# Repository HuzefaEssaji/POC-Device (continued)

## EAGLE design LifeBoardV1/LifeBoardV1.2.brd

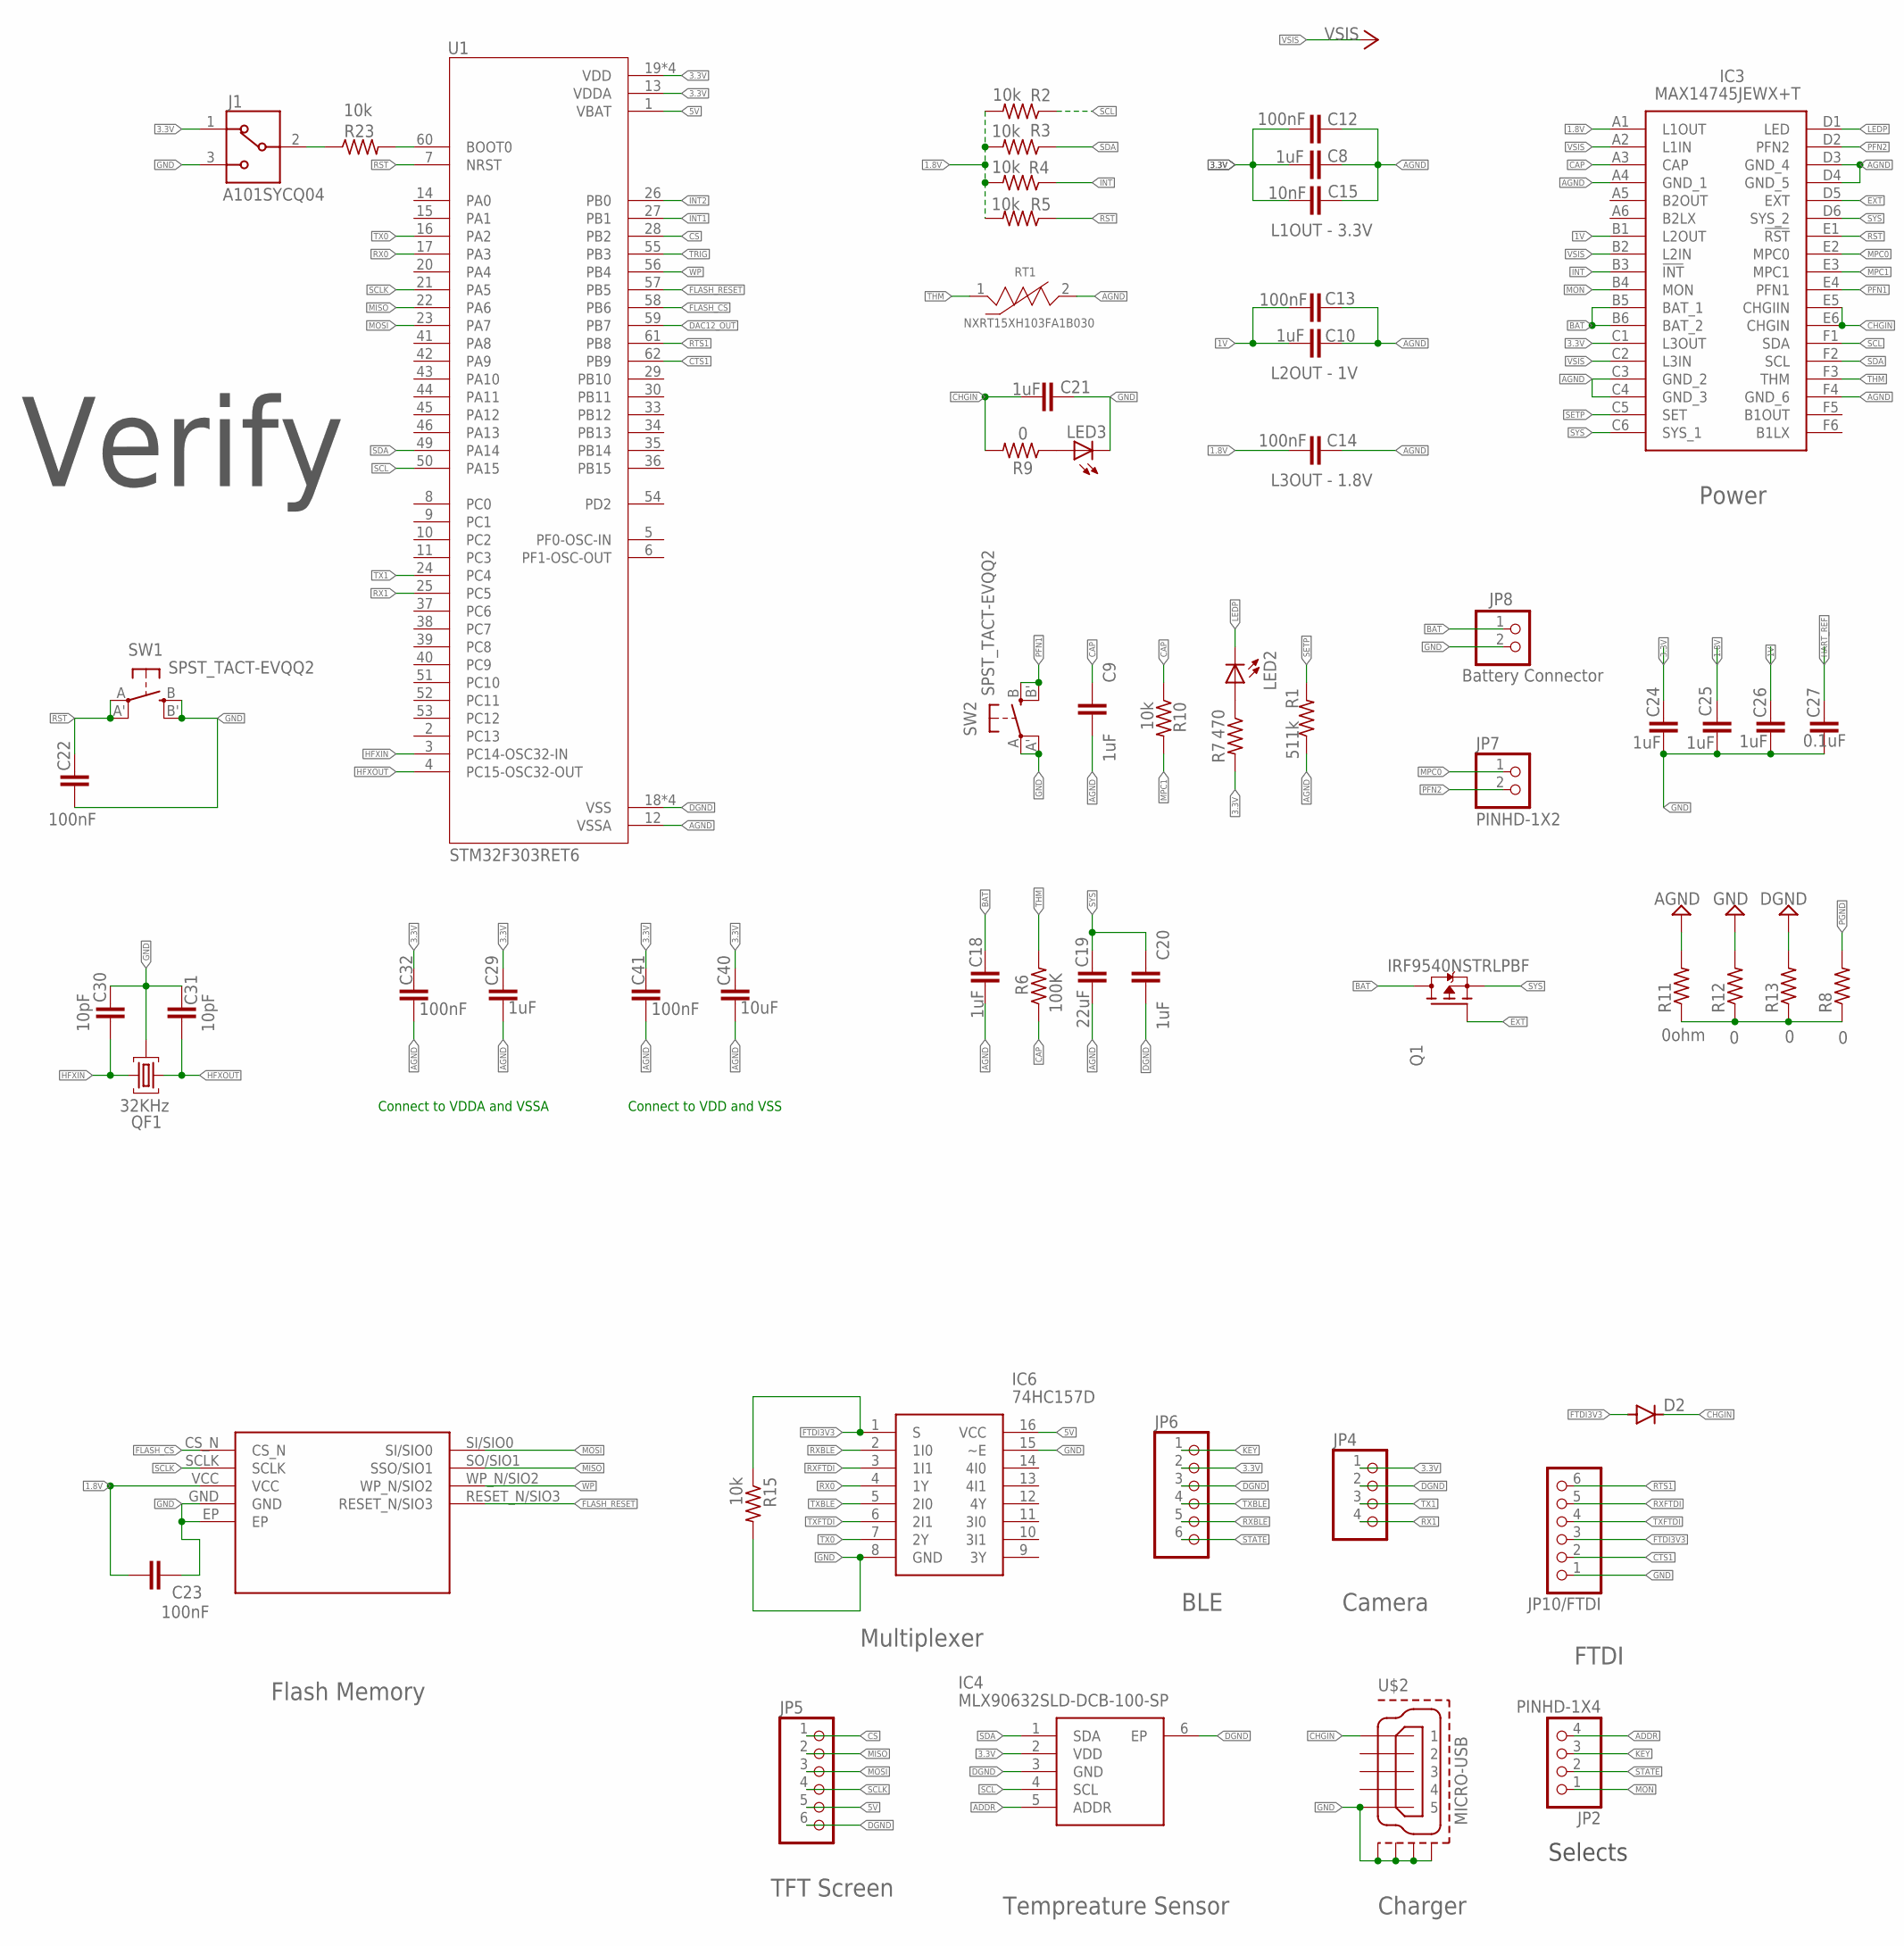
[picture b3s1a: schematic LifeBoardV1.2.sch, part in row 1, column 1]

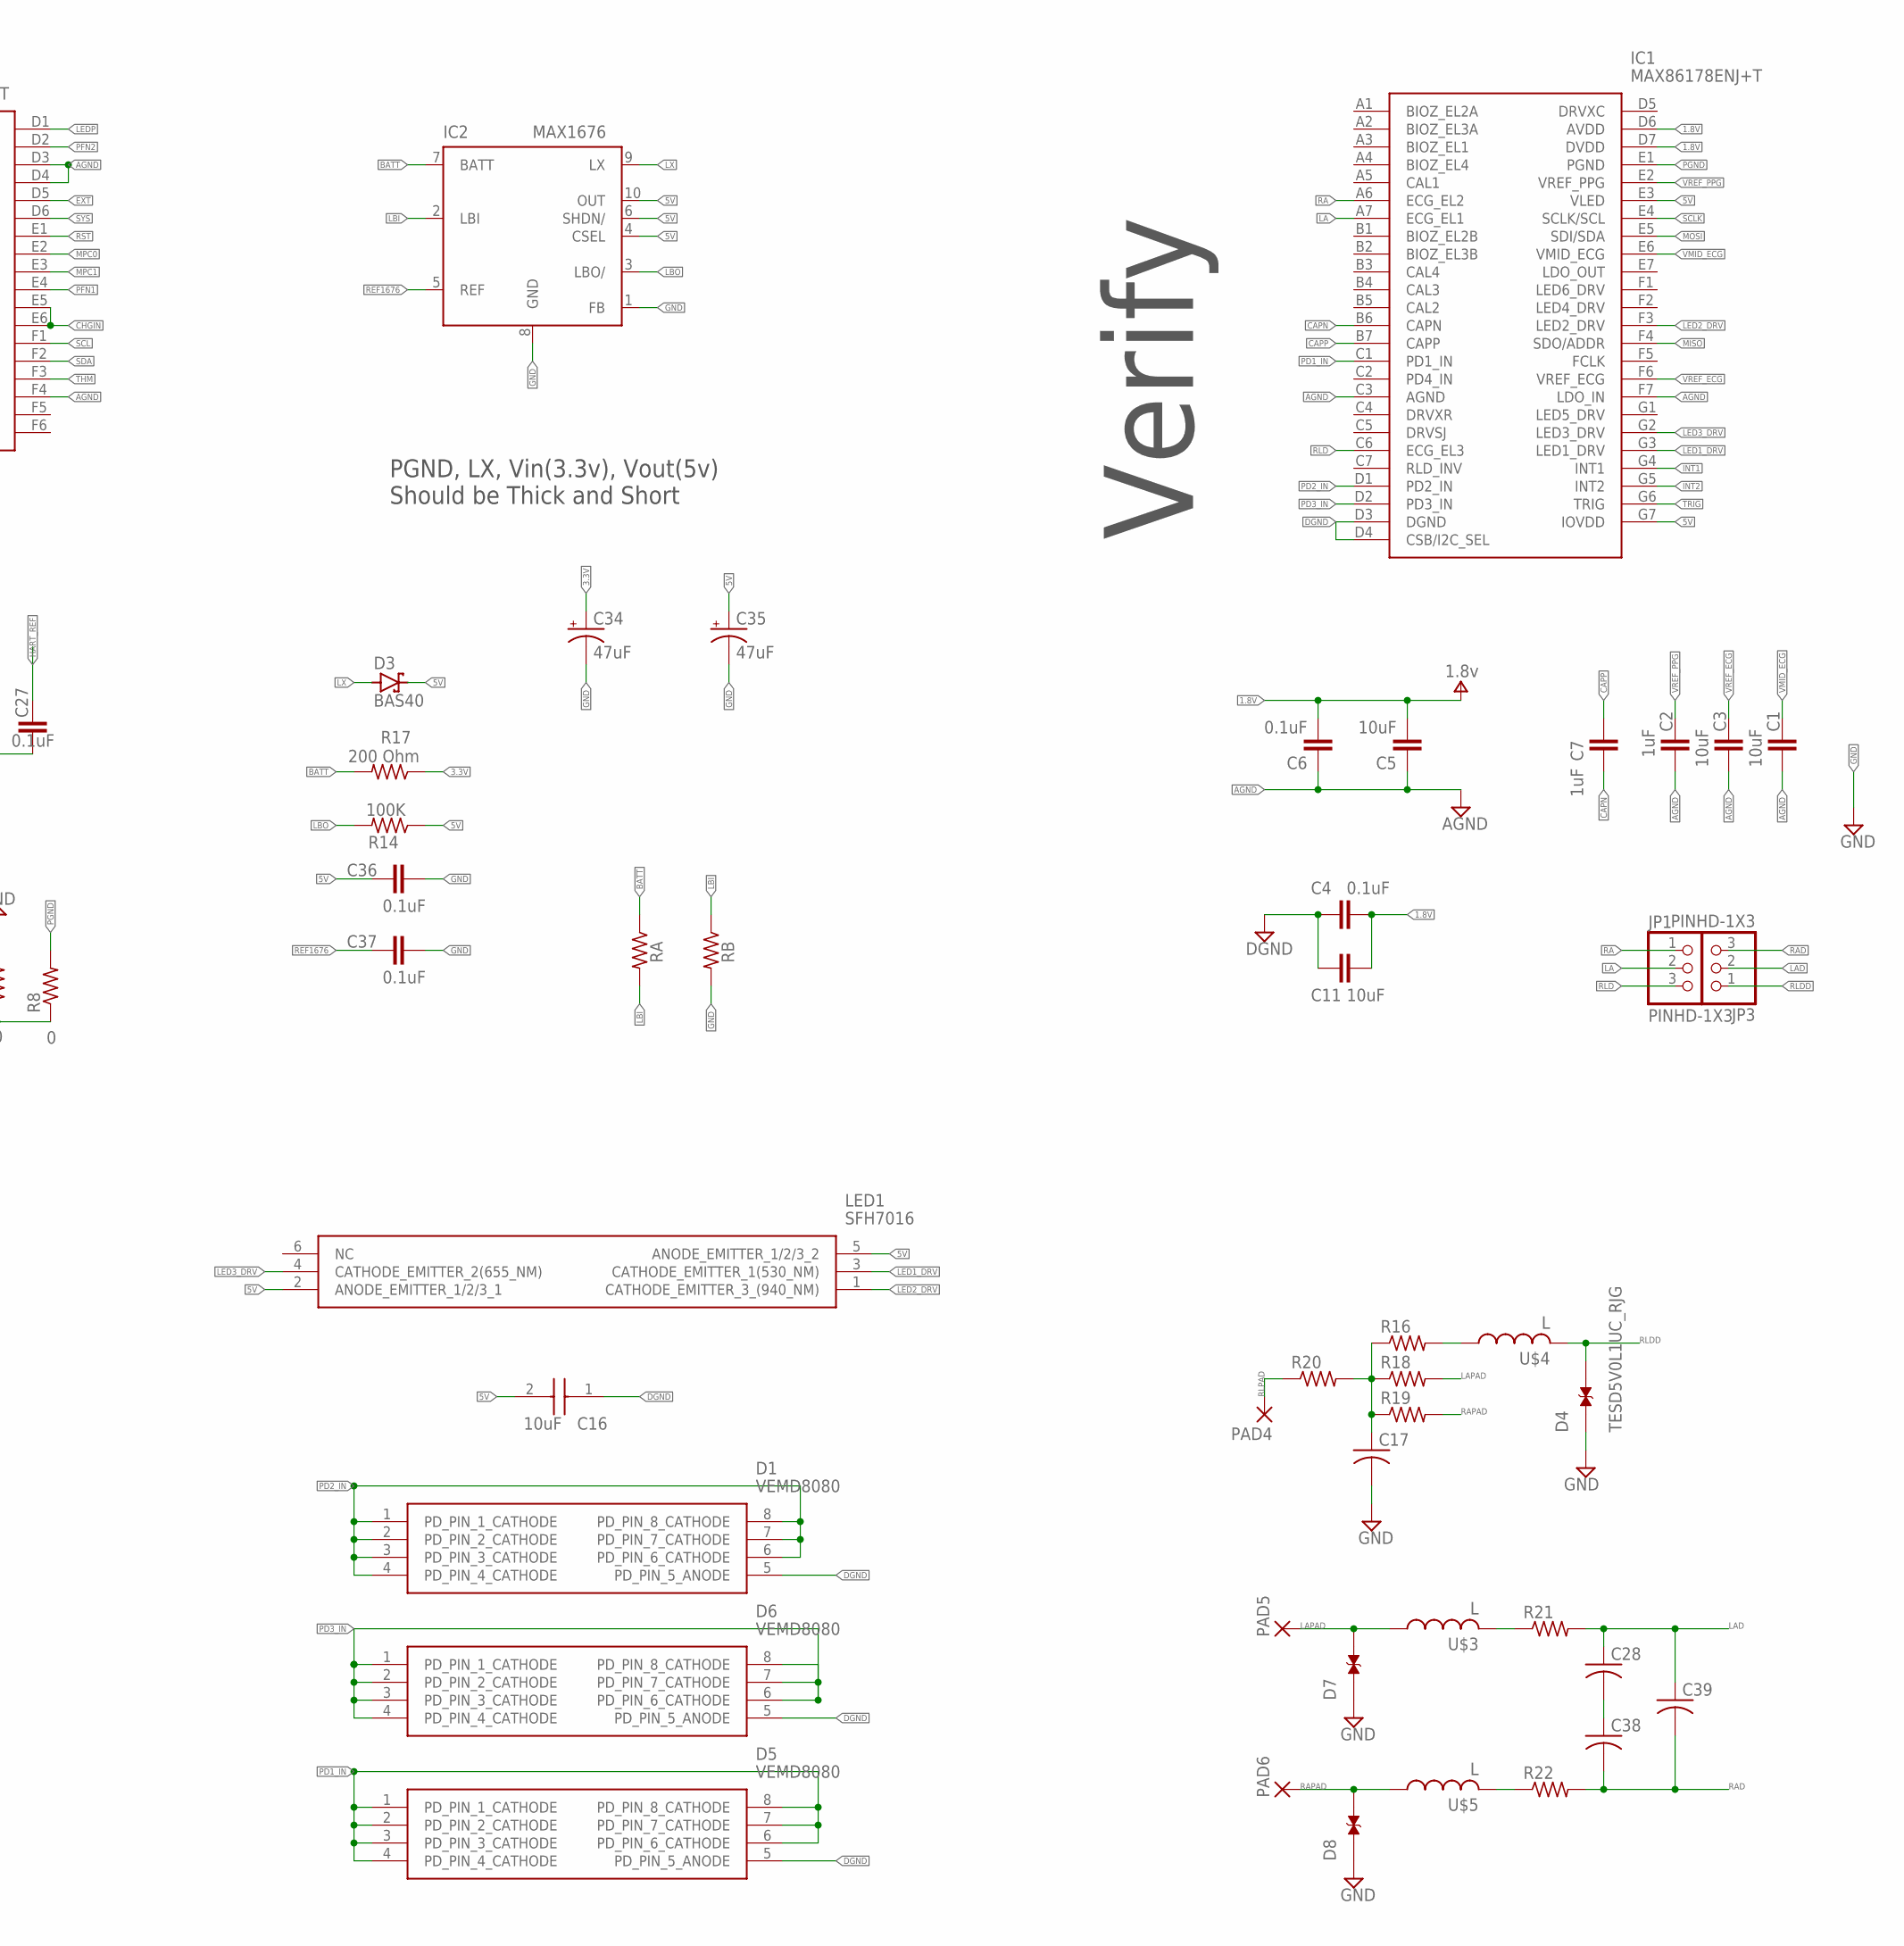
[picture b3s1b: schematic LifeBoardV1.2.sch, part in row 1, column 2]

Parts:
C1, C3, C5, C11, C40: 10uF; C0805
C2, C7, C8, C9, C10, C18, C20, C21, C24, C25, C26, C29: 1uF; C0805
C4, C6, C27, C36, C37: 0.1uF; C0805
C12, C13, C14, C22, C23, C32, C41: 100nF; C0805
C15: 10nF; C0805
C16: 10uF; CAPC1608X90N
C17, C28, C38, C39: C-US025-024X044; C025-024X044
C19: 22uF; C0805
C30, C31: 10pF; C0805
C34, C35: 47uF; 153CLV-0405
D1, D5, D6: VEMD8080
D2: CGRM4001-G; SOD-123_MINI-SMA
D3: BAS40; SOT23
D4, D7, D8: TESD5V0L1UC_RJG; DIO_TESD5V0L1UC_RJG
IC1: MAX86178ENJ+T; BGA49C35P7X7_277X257X50
IC2: MAX1676; UMAX10
IC3: MAX14745JEWX+T; BGA36C40P6X6_269X244X69
IC4: MLX90632SLD-DCB-100-SP; MLX90632SLDDCB100SP
IC6: 74HC157D; SOIC127P600X175-16N
J1: A101SYCQ04; TE_A101SYCQ04
JP1, JP3: PINHD-1X3; 1X03
JP2, JP4: PINHD-1X4; 1X04
JP5, JP6, JP10/FTDI: PINHD-1X6; 1X06
JP7: PINHD-1X2; 1X02
JP8: Battery Connector; 1X02
LED1: SFH7016
LED2, LED3: LEDCHIPLED_1206; CHIPLED_1206
PAD4, PAD5, PAD6: SMD5; SMD2,54-5,08
Q1: IRF9540NSTRLPBF; DPAK254P1524X483-4_3N
QF1: 32KHz; HC49U
R1: 511k; M1206
R2, R3, R4, R5, R10, R15, R23: 10k; M1206
R6: 100K; M1206
R7: 470; M1206
R8, R9, R12, R13: 0; R1206
R11: 0ohm; R1206
R14: 100K; R1206
R16, R18, R19, R20, R21, R22: R-US_0207/10; 0207/10
R17: 200 Ohm; R1206
RA: R-US_R1206; R1206
RB: R-US_R1206; R1206
RT1: NXRT15XH103FA1B030; THERM_NXRT15XH103FA1B030
SW1, SW2: SPST_TACT-EVQQ2; EVQ-Q2
U1: STM32F303RET6; QFP50P1200X1200X160-64N
U$1: FLASH; SON127P600X800X80-9N
U$2: MICRO-USB; 47589-0001
U$3, U$4, U$5: L; 6000

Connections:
1.8V: C4.2, C5.2, C6.2, C11.2, C14.2, C23.1, C25.1, IC1.D6 (AVDD), IC1.D7 (DVDD), IC3.A1 (L1OUT), R2.2, R3.2, R4.2, R5.2, U$1.VCC
1V: C10.2, C13.2, C26.1, IC3.B1 (L2OUT)
3.3V: C8.2, C12.2, C15.2, C24.1, C29.1, C32.1, C34.+, C40.1, C41.1, IC3.C1 (L3OUT), IC4.2 (VDD), J1.1, JP4.1, JP6.2, R7.2, R17.1, U1.13 (VDDA), U1.19 (VDD), U1.32 (VDD), U1.48 (VDD), U1.64 (VDD)
5V: C16.2, C35.+, C36.1, D3.3 (C), IC1.E3 (VLED), IC1.G7 (IOVDD), IC2.4 (CSEL), IC2.6 (SHDN/), IC2.10 (OUT), IC6.16 (VCC), JP5.5, LED1.2 (ANODE_EMITTER_1/2/3_1), LED1.5 (ANODE_EMITTER_1/2/3_2), R14.1, U1.1 (VBAT)
ADDR: IC4.5 (ADDR), JP2.4
AGND: C1.1, C2.1, C3.1, C5.1, C6.1, C8.1, C9.2, C10.1, C12.1, C13.1, C14.1, C15.1, C18.2, C19.2, C29.2, C32.2, C40.2, C41.2, IC1.C3 (AGND), IC1.F7 (LDO_IN), IC3.A4 (GND_1), IC3.C3 (GND_2), IC3.C4 (GND_3), IC3.D3 (GND_4), IC3.D4 (GND_5), IC3.F4 (GND_6), R1.1, R11.2, RT1.2, U1.12 (VSSA)
BAT: C18.1, IC3.B5 (BAT_1), IC3.B6 (BAT_2), JP8.1, Q1.4 (D)
BATT: IC2.7 (BATT), R17.2, RA.1
CAP: C9.1, IC3.A3 (CAP), R6.1, R10.1
CAPN: C7.2, IC1.B6 (CAPN)
CAPP: C7.1, IC1.B7 (CAPP)
CHGIN: C21.2, D2.C, IC3.E5 (CHGIIN), IC3.E6 (CHGIN), R9.2, U$2.1
CS: JP5.1, U1.28 (PB2)
CTS1: JP10/FTDI.2, U1.62 (PB9)
DAC12_OUT: U1.59 (PB7)
DGND: C4.1, C11.1, C16.1, C20.2, D1.5 (PD_PIN_5_ANODE), D5.5 (PD_PIN_5_ANODE), D6.5 (PD_PIN_5_ANODE), IC1.D3 (DGND), IC1.D4 (CSB/I2C_SEL), IC4.3 (GND), IC4.6 (EP), JP4.2, JP5.6, JP6.3, R13.2, U1.18 (VSS), U1.31 (VSS), U1.47 (VSS), U1.63 (VSS)
EXT: IC3.D5 (EXT), Q1.1 (G)
FLASH_CS: U1.58 (PB6), U$1.CS_N
FLASH_RESET: U1.57 (PB5), U$1.RESET_N/SIO3
FTDI3V3: D2.A, IC6.1 (S), JP10/FTDI.3, R15.1
GND: C17.2, C21.1, C22.2, C23.2, C24.2, C25.2, C26.2, C27.2, C30.1, C31.1, C34.-, C35.-, C36.2, C37.2, D4.1, D7.1, D8.1, IC2.1 (FB), IC2.8 (GND), IC6.8 (GND), IC6.15 (~E), J1.3, JP8.2, JP10/FTDI.1, LED3.C, QF1.2, R12.2, R15.2, RB.2, SW1.B (S), SW1.B' (S1), SW2.A, SW2.A' (P1), U$1.EP, U$1.GND, U$2.5, U$2.CASING1 (GND1), U$2.CASING2 (GND2), U$2.CASING3 (GND3), U$2.CASING4 (GND4)
HART_REF: C27.1
HFXIN: C30.2, QF1.3, U1.3 (PC14-OSC32-IN)
HFXOUT: C31.2, QF1.1, U1.4 (PC15-OSC32-OUT)
INT: IC3.B3 (!INT), R4.1
INT1: IC1.G4 (INT1), U1.27 (PB1)
INT2: IC1.G5 (INT2), U1.26 (PB0)
KEY: JP2.3, JP6.1
LA: IC1.A7 (ECG_EL1), JP1.2
LAD: C28.1, C39.1, JP3.2, R21.2
LAPAD: D7.2, PAD5.1, R18.2, U$3.1
LBI: IC2.2 (LBI), RA.2, RB.1
LBO: IC2.3 (LBO/), R14.2
LED1_DRV: IC1.G3 (LED1_DRV), LED1.3 (CATHODE_EMITTER_1(530_NM))
LED2_DRV: IC1.F3 (LED2_DRV), LED1.1 (CATHODE_EMITTER_3_(940_NM))
LED3_DRV: IC1.G2 (LED3_DRV), LED1.4 (CATHODE_EMITTER_2(655_NM))
LEDP: IC3.D1 (LED), LED2.C
LX: D3.1 (A), IC2.9 (LX)
MISO: IC1.F4 (SDO/ADDR), JP5.2, U1.22 (PA6), U$1.SO/SIO1 (SSO/SIO1)
MON: IC3.B4 (MON), JP2.1
MOSI: IC1.E5 (SDI/SDA), JP5.3, U1.23 (PA7), U$1.SI/SIO0
MPC0: IC3.E2 (MPC0), JP7.1
MPC1: IC3.E3 (MPC1), R10.2
unnamed: LED2.A, R7.1
unnamed: C17.1, R16.1, R18.1, R19.1, R20.2
unnamed: R16.2, U$4.1
unnamed: R23.2, U1.60 (BOOT0)
unnamed: J1.2, R23.1
unnamed: R21.1, U$3.2
unnamed: C28.2, C38.1
unnamed: R22.1, U$5.2
unnamed: R8.1, R11.1, R12.1, R13.1
unnamed: LED3.A, R9.1
PD1_IN: D5.1 (PD_PIN_1_CATHODE), D5.2 (PD_PIN_2_CATHODE), D5.3 (PD_PIN_3_CATHODE), D5.4 (PD_PIN_4_CATHODE), D5.6 (PD_PIN_6_CATHODE), D5.7 (PD_PIN_7_CATHODE), D5.8 (PD_PIN_8_CATHODE), IC1.C1 (PD1_IN)
PD2_IN: D1.1 (PD_PIN_1_CATHODE), D1.2 (PD_PIN_2_CATHODE), D1.3 (PD_PIN_3_CATHODE), D1.4 (PD_PIN_4_CATHODE), D1.6 (PD_PIN_6_CATHODE), D1.7 (PD_PIN_7_CATHODE), D1.8 (PD_PIN_8_CATHODE), IC1.D1 (PD2_IN)
PD3_IN: D6.1 (PD_PIN_1_CATHODE), D6.2 (PD_PIN_2_CATHODE), D6.3 (PD_PIN_3_CATHODE), D6.4 (PD_PIN_4_CATHODE), D6.6 (PD_PIN_6_CATHODE), D6.7 (PD_PIN_7_CATHODE), D6.8 (PD_PIN_8_CATHODE), IC1.D2 (PD3_IN)
PFN1: IC3.E4 (PFN1), SW2.B (S), SW2.B' (S1)
PFN2: IC3.D2 (PFN2), JP7.2
PGND: IC1.E1 (PGND), R8.2
RA: IC1.A6 (ECG_EL2), JP1.1
RAD: C38.2, C39.2, JP3.3, R22.2
RAPAD: D8.2, PAD6.1, R19.2, U$5.1
REF1676: C37.1, IC2.5 (REF)
RLD: IC1.C6 (ECG_EL3), JP1.3
RLDD: D4.2, JP3.1, U$4.2
RLPAD: PAD4.1, R20.1
RST: C22.1, IC3.E1 (!RST), R5.1, SW1.A, SW1.A' (P1), U1.7 (NRST)
RTS1: JP10/FTDI.6, U1.61 (PB8)
RX0: IC6.4 (1Y), U1.17 (PA3)
RX1: JP4.4, U1.25 (PC5)
RXBLE: IC6.2 (1I0), JP6.5
RXFTDI: IC6.3 (1I1), JP10/FTDI.5
SCL: IC3.F1 (SDA), IC4.4 (SCL), R2.1, U1.50 (PA15)
SCLK: IC1.E4 (SCLK/SCL), JP5.4, U1.21 (PA5), U$1.SCLK
SDA: IC3.F2 (SCL), IC4.1 (SDA), R3.1, U1.49 (PA14)
SETP: IC3.C5 (SET), R1.2
STATE: JP2.2, JP6.6
SYS: C19.1, C20.1, IC3.C6 (SYS_1), IC3.D6 (SYS_2), Q1.3 (S)
THM: IC3.F3 (THM), R6.2, RT1.1
TRIG: IC1.G6 (TRIG), U1.55 (PB3)
TX0: IC6.7 (2Y), U1.16 (PA2)
TX1: JP4.3, U1.24 (PC4)
TXBLE: IC6.5 (2I0), JP6.4
TXFTDI: IC6.6 (2I1), JP10/FTDI.4
VMID_ECG: C1.2, IC1.E6 (VMID_ECG)
VREF_ECG: C3.2, IC1.F6 (VREF_ECG)
VREF_PPG: C2.2, IC1.E2 (VREF_PPG)
VSIS: IC3.A2 (L1IN), IC3.B2 (L2IN), IC3.C2 (L3IN)
WP: U1.56 (PB4), U$1.WP_N/SIO2

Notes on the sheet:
L1OUT - 3.3V
L2OUT - 1V
L3OUT - 1.8V
BLE
FTDI
Charger
Flash Memory
Tempreature Sensor
Power
Camera
TFT Screen
Multiplexer
PGND, LX, Vin(3.3v), Vout(5v) Should be Thick and Short
Selects
Connect to VDD and VSS
Connect to VDDA and VSSA
Verify

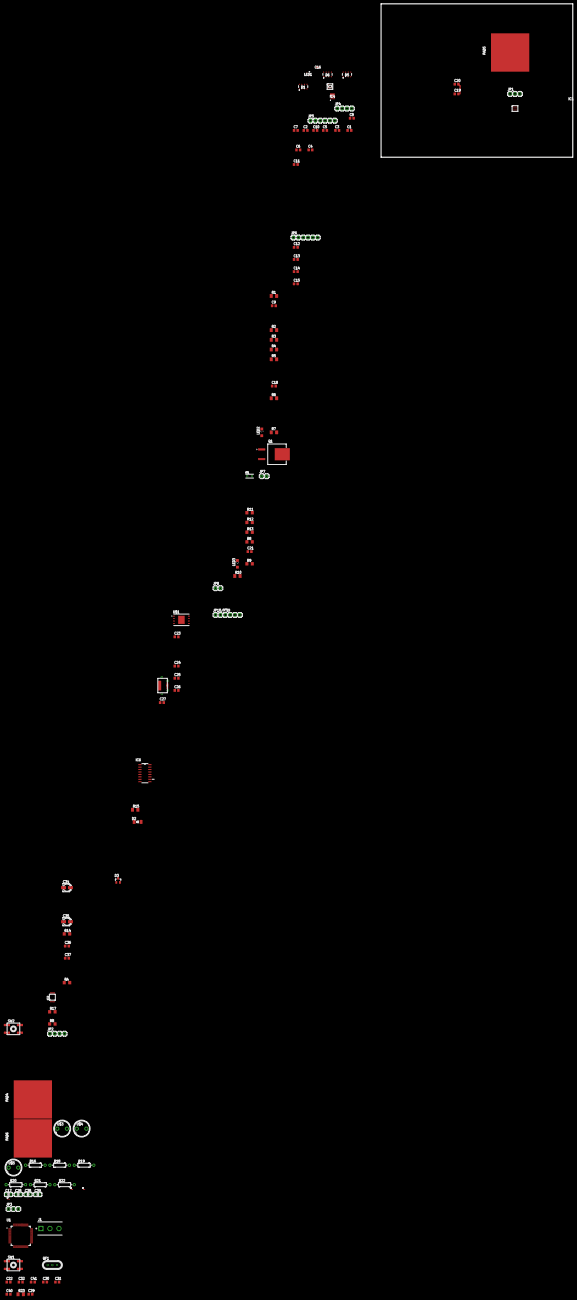
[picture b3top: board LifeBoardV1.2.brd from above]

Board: 2 copper layers, 100.0 x 80.0 mm, 105 parts (0 on the bottom side), 87 nets.

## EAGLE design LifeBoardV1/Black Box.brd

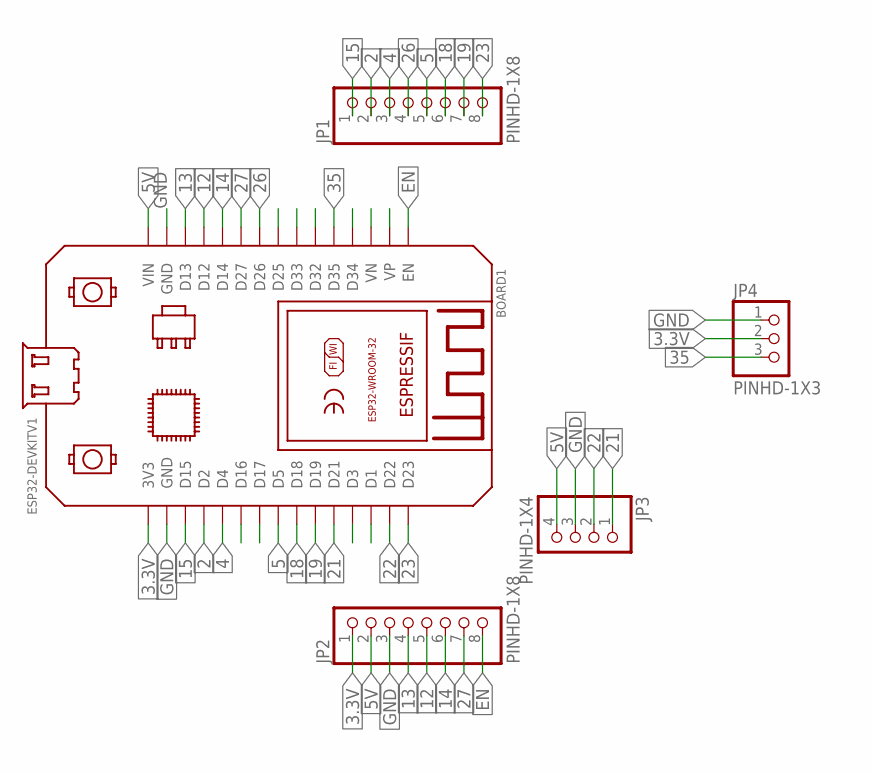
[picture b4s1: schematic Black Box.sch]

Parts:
BOARD1: ESP32DEVKITV1; ESP32-DEVKITV1
JP1, JP2: PINHD-1X8; 1X08
JP3: PINHD-1X4; 1X04
JP4: PINHD-1X3; 1X03

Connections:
2: BOARD1.D2, JP1.2
3.3V: BOARD1.3V3, JP2.1, JP4.2
4: BOARD1.D4, JP1.3
5: BOARD1.D5, JP1.5
5V: BOARD1.VIN, JP2.2, JP3.4
12: BOARD1.D12, JP2.5
13: BOARD1.D13, JP2.4
14: BOARD1.D14, JP2.6
15: BOARD1.D15, JP1.1
18: BOARD1.D18, JP1.6
19: BOARD1.D19, JP1.7
21: BOARD1.D21, JP3.1
22: BOARD1.D22, JP3.2
23: BOARD1.D23, JP1.8
26: BOARD1.D26, JP1.4
27: BOARD1.D27, JP2.7
35: BOARD1.D35, JP4.3
EN: BOARD1.EN, JP2.8
GND: BOARD1.GND, BOARD1.GND@1 (GND), JP2.3, JP3.3, JP4.1

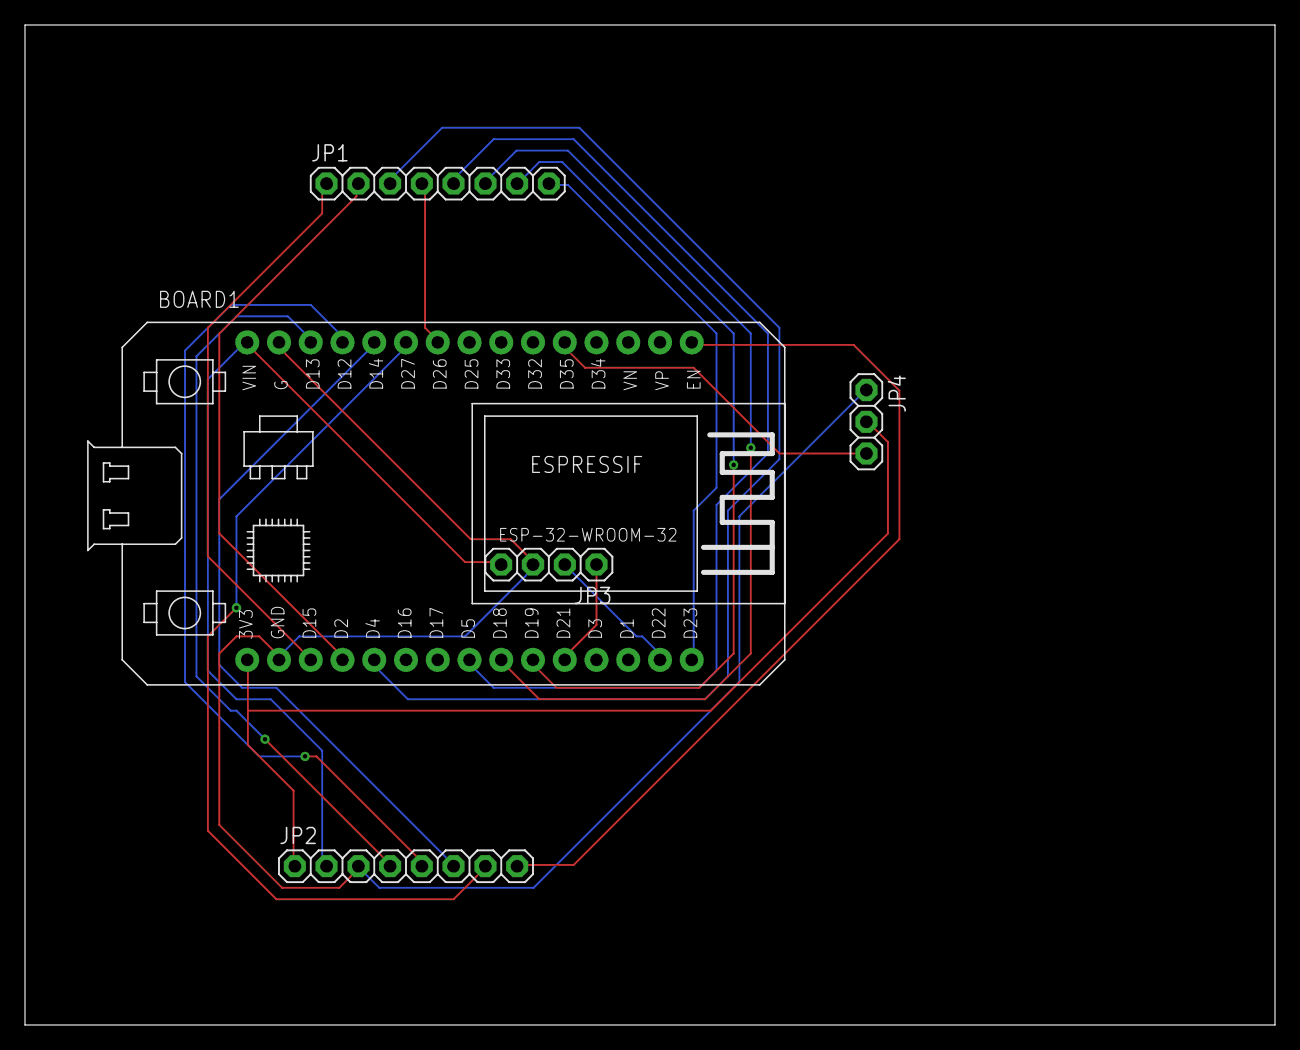
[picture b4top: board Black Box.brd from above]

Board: 2 copper layers, 100.0 x 80.0 mm, 5 parts (0 on the bottom side), 19 nets.

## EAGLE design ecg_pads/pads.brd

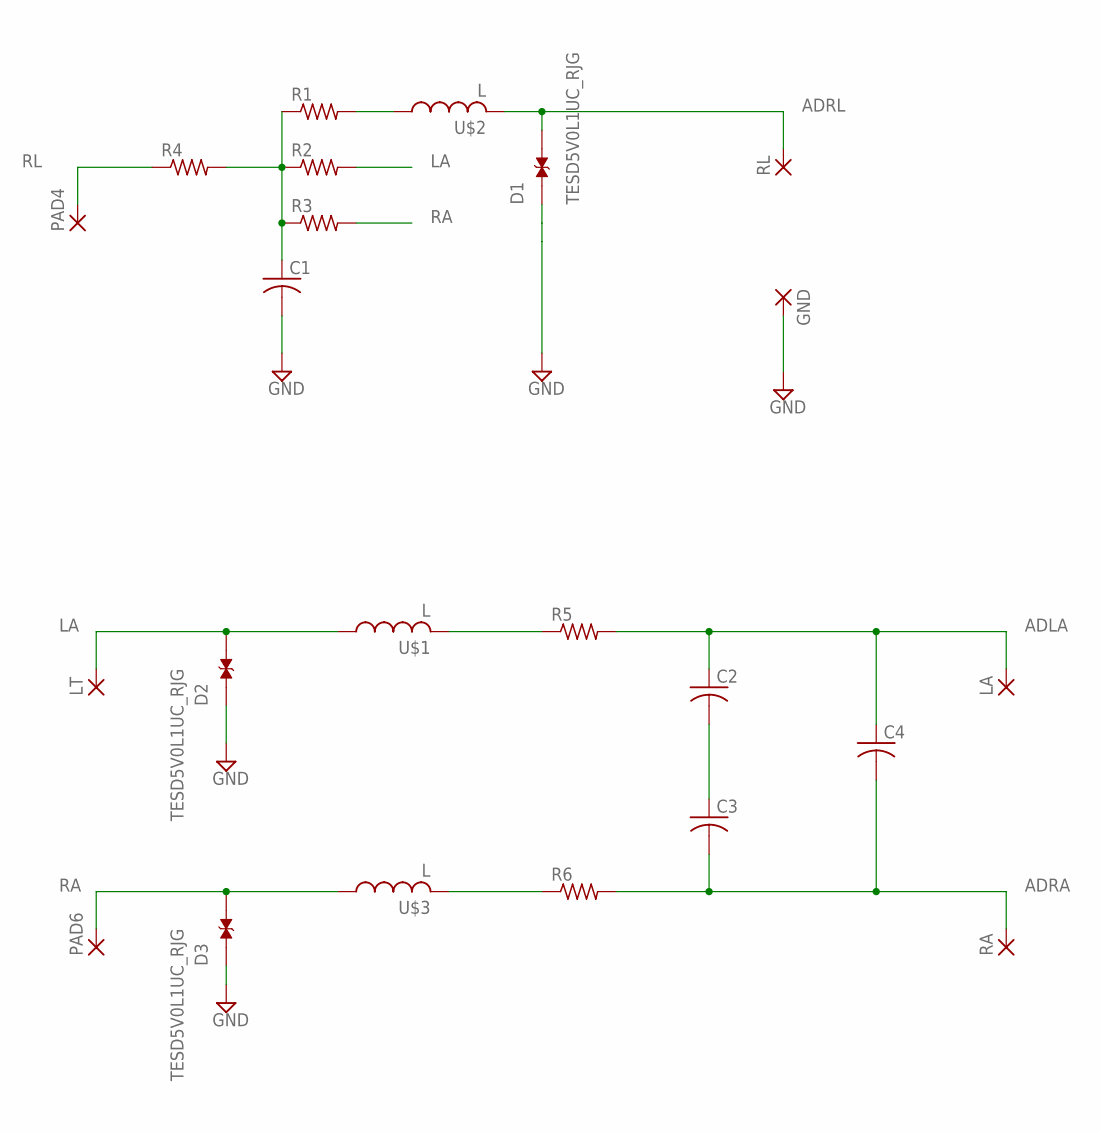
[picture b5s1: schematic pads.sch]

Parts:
C1, C2, C3, C4: C-US025-024X044; C025-024X044
D1, D2, D3: TESD5V0L1UC_RJG; DIO_TESD5V0L1UC_RJG
GND: 2,15/1,0
LA: 2,15/1,0
LT: SMD5; SMD2,54-5,08
PAD4, PAD6: SMD5; SMD2,54-5,08
R1, R2, R3, R4, R5, R6: R-US_0207/10; 0207/10
RA: 2,15/1,0
RL: 2,15/1,0
U$1, U$2, U$3: L; 6000

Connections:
ADLA: C2.1, C4.1, LA.1, R5.2
ADRA: C3.2, C4.2, R6.2, RA.1
ADRL: D1.2, RL.1, U$2.2
GND: C1.2, D1.1, D2.1, D3.1, GND.1
LA: D2.2, LT.1, R2.2, U$1.1
unnamed: C1.1, R1.1, R2.1, R3.1, R4.2
unnamed: R1.2, U$2.1
unnamed: R5.1, U$1.2
unnamed: C2.2, C3.1
unnamed: R6.1, U$3.2
RA: D3.2, PAD6.1, R3.2, U$3.1
RL: PAD4.1, R4.1

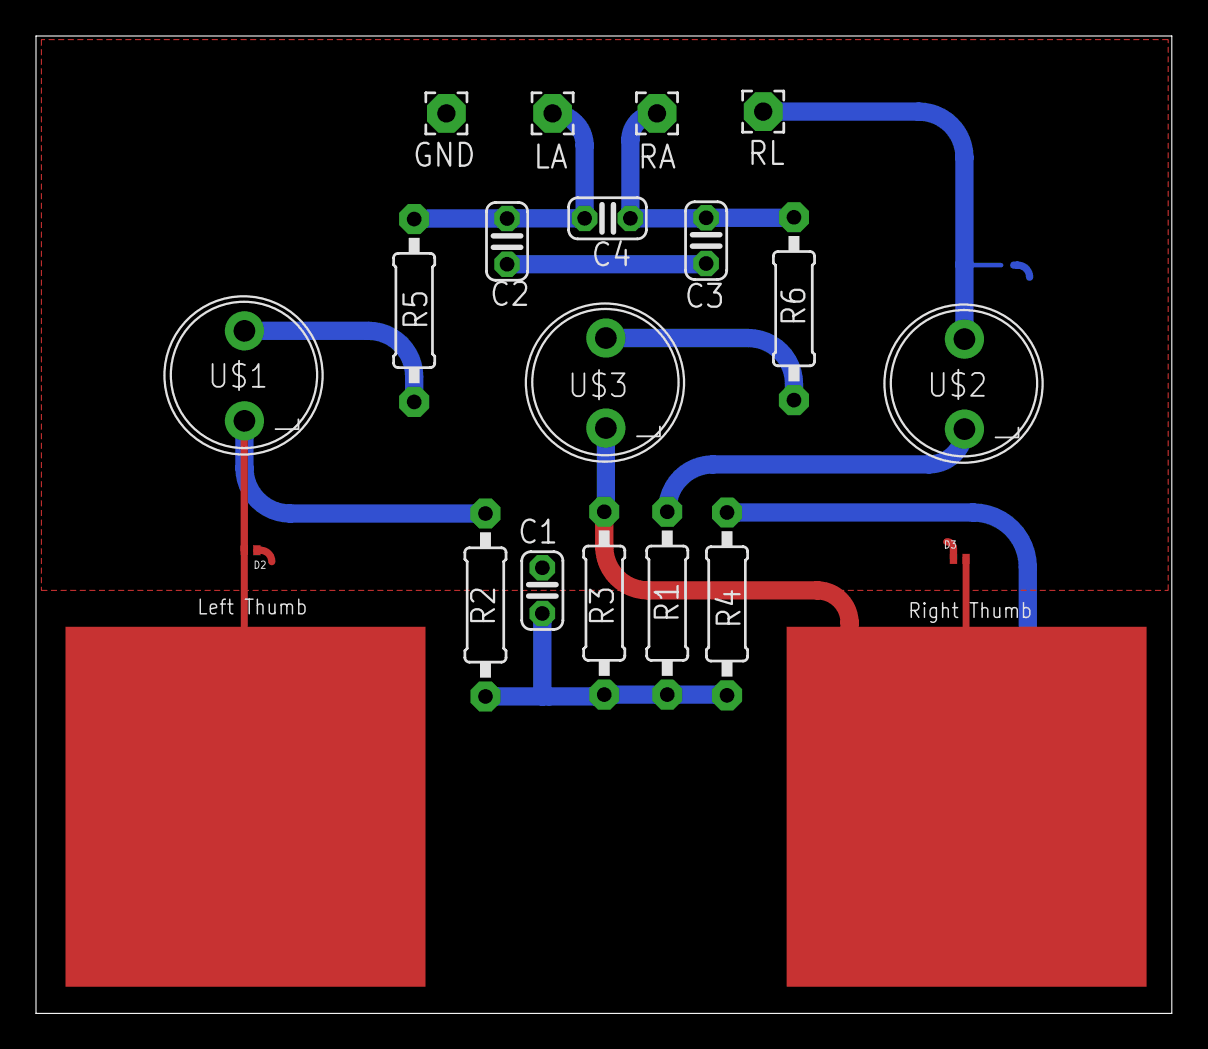
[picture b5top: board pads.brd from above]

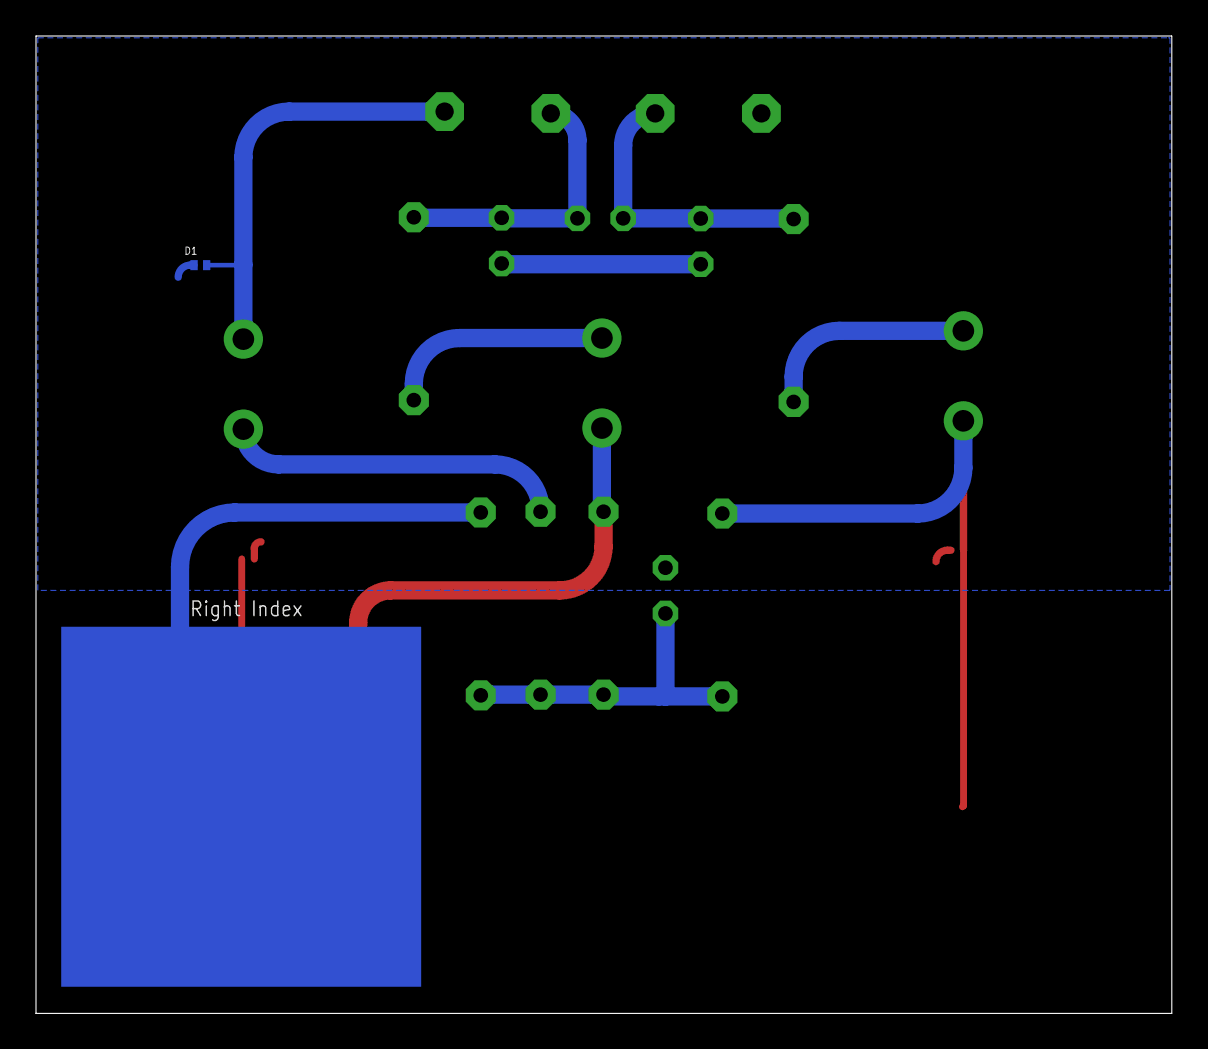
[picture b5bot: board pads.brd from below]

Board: 2 copper layers, 63.1 x 54.3 mm, 23 parts (2 on the bottom side), 12 nets.

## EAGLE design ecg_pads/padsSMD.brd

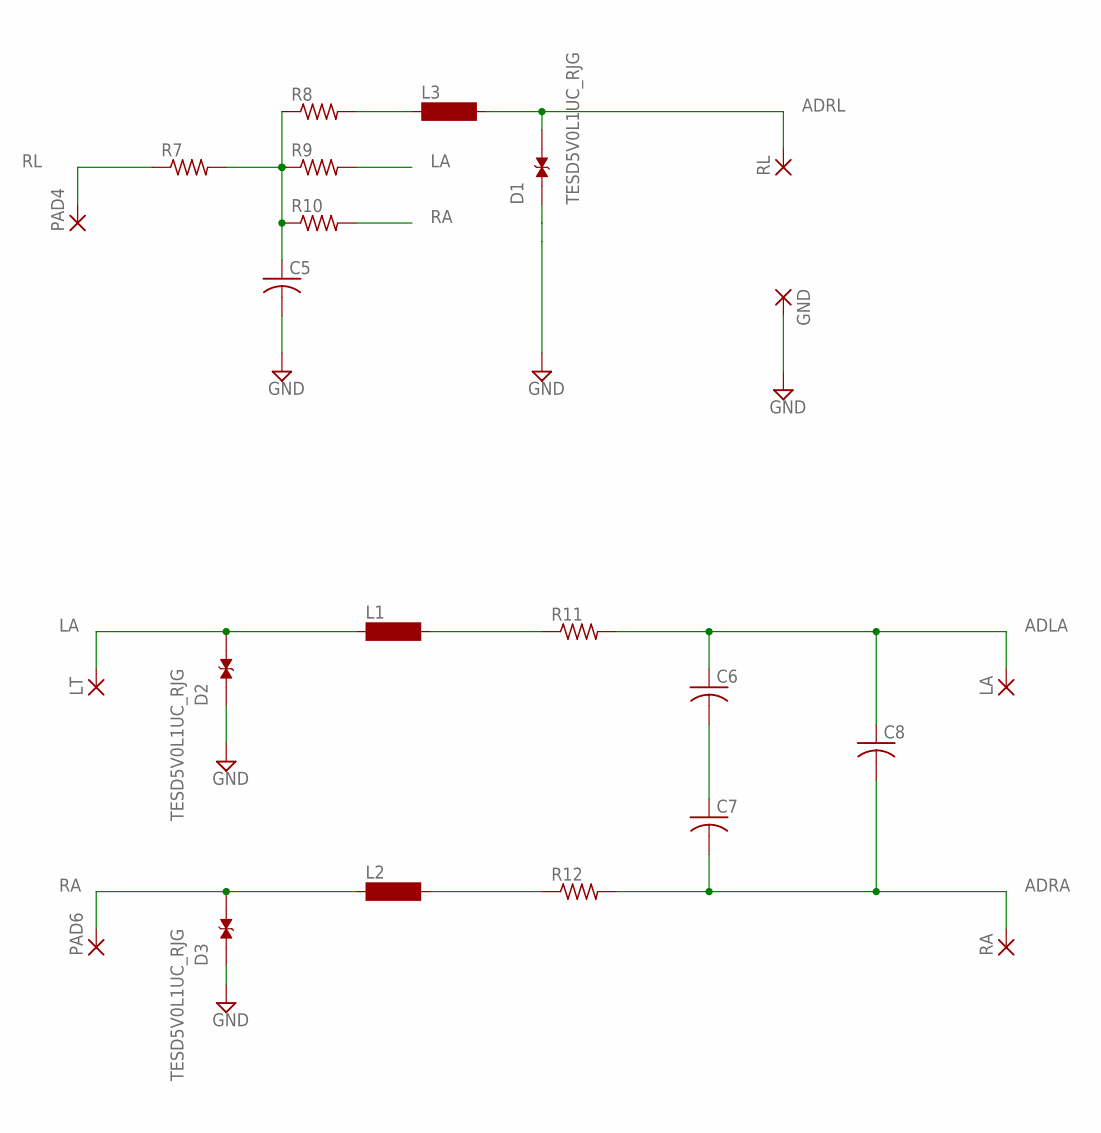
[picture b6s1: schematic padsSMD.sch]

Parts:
C5, C6, C7, C8: C-USC1206; C1206
D1, D2, D3: TESD5V0L1UC_RJG; DIO_TESD5V0L1UC_RJG
GND: 2,15/1,0
L1, L2, L3: SM-1206
LA: 2,15/1,0
LT: SMD5; SMD2,54-5,08
PAD4, PAD6: SMD5; SMD2,54-5,08
R7, R8, R9, R10, R11, R12: R-US_R1206; R1206
RA: 2,15/1,0
RL: 2,15/1,0

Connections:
ADLA: C6.1, C8.1, LA.1, R11.2
ADRA: C7.2, C8.2, R12.2, RA.1
ADRL: D1.2, L3.2, RL.1
GND: C5.2, D1.1, D2.1, D3.1, GND.1
LA: D2.2, L1.1, LT.1, R9.2
unnamed: C5.1, R7.2, R8.1, R9.1, R10.1
unnamed: L3.1, R8.2
unnamed: L1.2, R11.1
unnamed: C6.2, C7.1
unnamed: L2.2, R12.1
RA: D3.2, L2.1, PAD6.1, R10.2
RL: PAD4.1, R7.1
